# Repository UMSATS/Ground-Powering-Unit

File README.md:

# Ground-Powering-Unit
This is a repository to collaborate on the ground powering unit PCB for the UMSATS rocket.

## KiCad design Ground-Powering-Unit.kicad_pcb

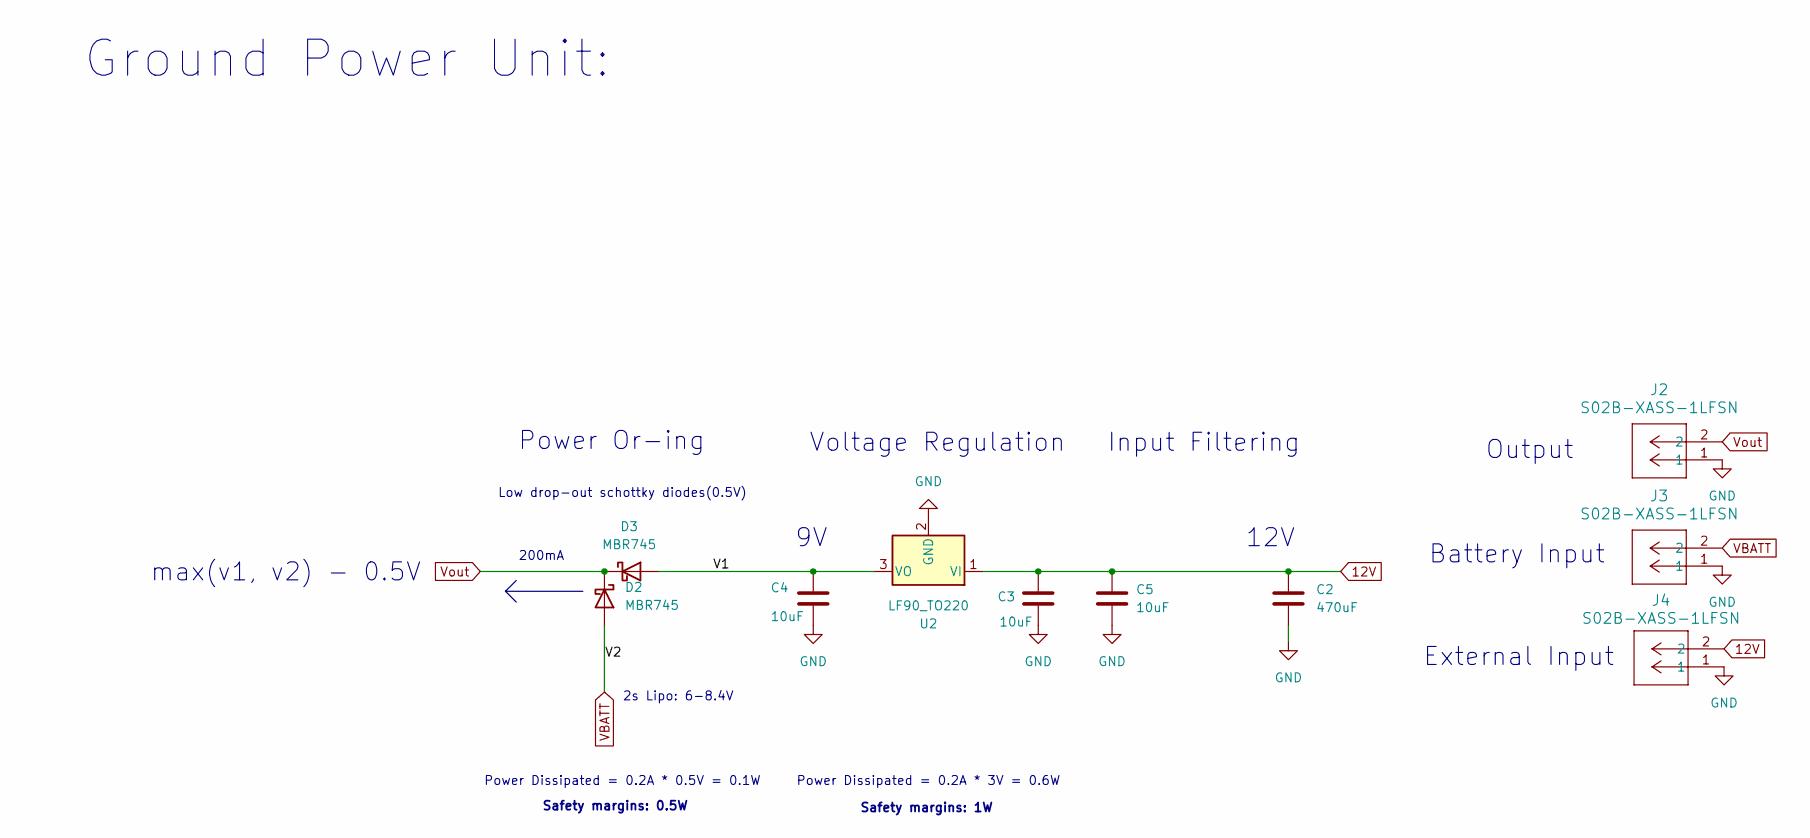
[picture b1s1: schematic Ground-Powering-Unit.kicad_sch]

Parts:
C2: 470uF; CP_Radial_D8.0mm_P3.50mm
C3, C4, C5: 10uF; C_1210_3225Metric_Pad1.33x2.70mm_HandSolder
D2, D3: MBR745; TO-220-2_Vertical
J2, J3, J4: S02B-XASS-1LFSN; CONN2_S02B-XASS_295x496_JST
U2: LF90_TO220; TO-220-3_Vertical

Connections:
12V: C2.1, C3.1, C5.1, J4.2, U2.1 (VI)
/V1: C4.1, D3.2 (A), U2.3 (VO)
GND: C2.2, C3.2, C4.2, C5.2, J2.1, J3.1, J4.1, U2.2 (GND)
VBATT: D2.2 (A), J3.2
Vout: D2.1 (K), D3.1 (K), J2.2

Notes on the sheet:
External Input
Low drop-out schottky diodes(0.5V)
Voltage Regulation
Output
Power Dissipated = 0.2A * 3V = 0.6W
Safety margins: 0.5W
max(v1, v2) - 0.5V
Power Dissipated = 0.2A * 0.5V = 0.1W
2s Lipo: 6-8.4V
200mA
Input Filtering
Power Or-ing
Safety margins: 1W
Ground Power Unit:
12V
Battery Input

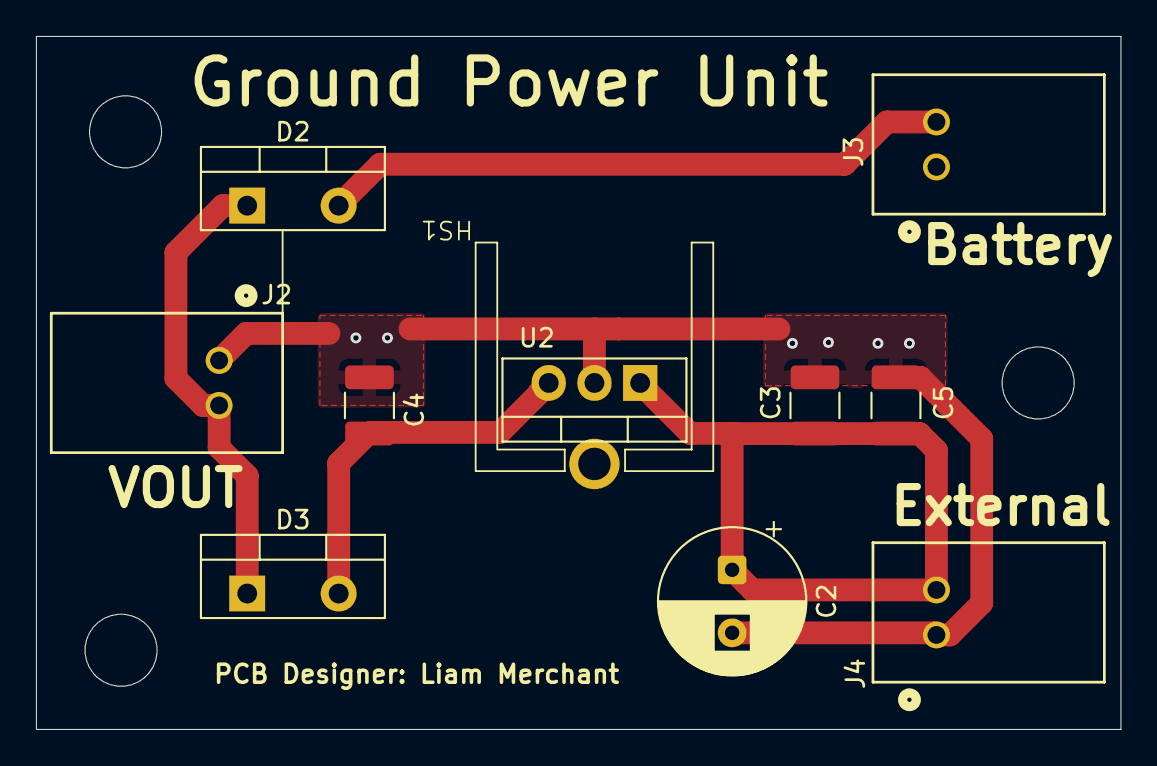
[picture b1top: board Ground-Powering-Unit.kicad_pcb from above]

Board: 2 copper layers, 60.2 x 38.5 mm, 11 parts (0 on the bottom side), 5 nets.

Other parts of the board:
HS1: V7237C_Heatsink
